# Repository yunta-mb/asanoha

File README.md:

# Asanoha keyboard

## Features:
* ZMK
* XIAO BLE (nRF52840)
* Bluetooth and/or USB
* Wireless split
* 42 sockets for Kailh Choc
* Every switch has its own GPIO - no matrix scanning needed, just interrupts
* Light af
* Low profile
* True well (not just raised keycaps), with customizable angle 
* Hardware power switch
* FDM-printable chassis
* Works for months on a single charge

## Building firmware

In devcontainer:
```
west update
west build -p -b xiao_ble -S studio-rpc-usb-uart   -- -DSHIELD=asanoha_left  -DZMK_EXTRA_MODULES=/workspaces/zmk-modules/zmk-keyboard-asanoha/
west build -p -b xiao_ble -S studio-rpc-usb-uart   -- -DSHIELD=asanoha_right -DZMK_EXTRA_MODULES=/workspaces/zmk-modules/zmk-keyboard-asanoha/
```

## More photos

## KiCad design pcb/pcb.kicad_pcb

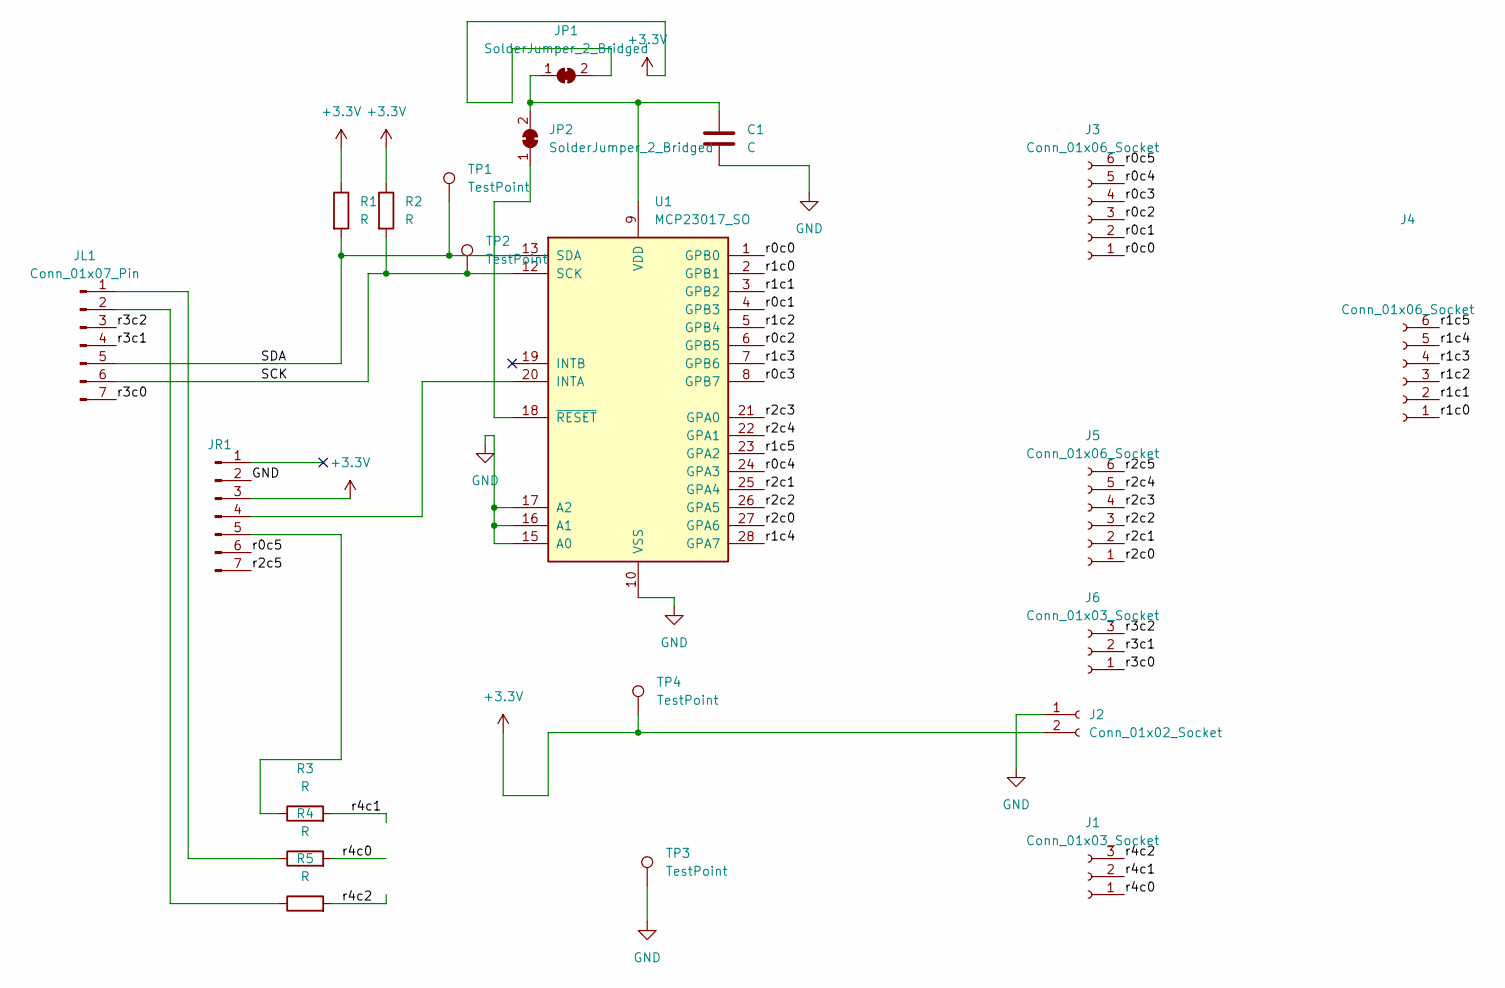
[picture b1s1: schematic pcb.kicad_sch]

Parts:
C1: C; C_0805_2012Metric_Pad1.18x1.45mm_HandSolder
J1, J6: Conn_01x03_Socket; SolderWire-0.1sqmm_1x03_P3.6mm_D0.4mm_OD1mm-dense-row-1
J2: Conn_01x02_Socket; SolderWire-0.1sqmm_1x02_P3.6mm_D0.4mm_OD1mm-dense-1
J3, J4, J5: Conn_01x06_Socket; SolderWire-0.1sqmm_1x06_P3.6mm_D0.4mm_OD1mm-dense-row-1
JL1: Conn_01x07_Pin; PinHeader_1x07_P2.54mm_Vertical-no-frame
JP1, JP2: SolderJumper_2_Bridged; SolderJumper-2_P1.3mm_Bridged_RoundedPad1.0x1.5mm
JR1: Conn_01x07_Pin; PinHeader_1x07_P2.54mm_Vertical-no-frame
R1, R2, R3, R4, R5: R; R_0603_1608Metric_Pad0.98x0.95mm_HandSolder
TP1, TP2, TP3, TP4: TestPoint; TestPoint_Pad_1.5x1.5mm
U1: MCP23017_SO; SSOP-28_5.3x10.2mm_P0.65mm

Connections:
+3.3V: J2.2, JP1.2 (B), JR1.3, R1.1, R2.1, TP4.1
/SCK: JL1.6, R2.2, TP2.1, U1.12 (SCK)
/SDA: JL1.5, R1.2, TP1.1, U1.13 (SDA)
/r0c0: J3.1, U1.1 (GPB0)
/r0c1: J3.2, U1.4 (GPB3)
/r0c2: J3.3, U1.6 (GPB5)
/r0c3: J3.4, U1.8 (GPB7)
/r0c4: J3.5, U1.24 (GPA3)
/r0c5: J3.6, JR1.6
/r1c0: J4.1, U1.2 (GPB1)
/r1c1: J4.2, U1.3 (GPB2)
/r1c2: J4.3, U1.5 (GPB4)
/r1c3: J4.4, U1.7 (GPB6)
/r1c4: J4.5, U1.28 (GPA7)
/r1c5: J4.6, U1.23 (GPA2)
/r2c0: J5.1, U1.27 (GPA6)
/r2c1: J5.2, U1.25 (GPA4)
/r2c2: J5.3, U1.26 (GPA5)
/r2c3: J5.4, U1.21 (GPA0)
/r2c4: J5.5, U1.22 (GPA1)
/r2c5: J5.6, JR1.7
/r3c0: J6.1, JL1.7
/r3c1: J6.2, JL1.4
/r3c2: J6.3, JL1.3
/r4c0: J1.1, R4.2
/r4c1: J1.2, R3.2
/r4c2: J1.3, R5.2
GND: C1.2, J2.1, JR1.2, TP3.1, U1.10 (VSS), U1.15 (A0), U1.16 (A1), U1.17 (A2)
unnamed: JL1.1, R4.1
unnamed: JL1.2, R5.1
unnamed: C1.1, JP1.1 (A), JP2.2 (B), U1.9 (VDD)
unnamed: JP2.1 (A), U1.18 (~RESET)
unnamed: JR1.4, U1.20 (INTA)
unnamed: JR1.5, R3.1

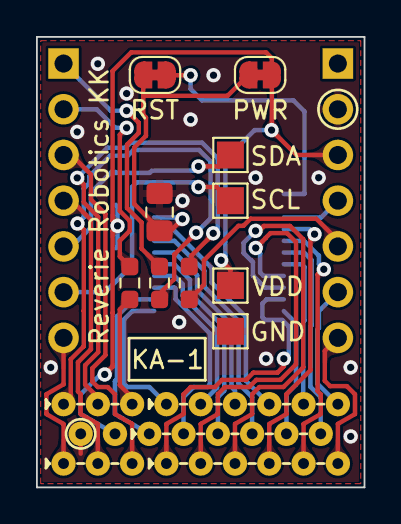
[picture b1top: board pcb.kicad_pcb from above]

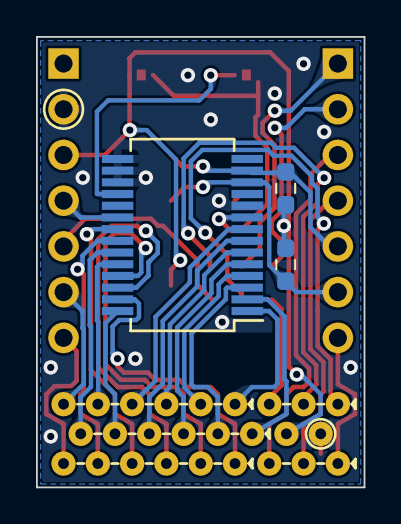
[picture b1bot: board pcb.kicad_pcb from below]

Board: 2 copper layers, 18.2 x 25.0 mm, 21 parts (5 on the bottom side), 34 nets.

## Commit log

2026-04-08 Swap jpegs for not arithmetic coded
